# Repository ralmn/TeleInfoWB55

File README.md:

# TeleInfo - ST32WB55

[Version Française / French version](README.FR.md)

This project allows to get the information from the French Linky electric meters (and old meters) via the customer tele-information terminals "TIC" and transmit them in Zigbee. The module is powered by the 150mW dedicated power supply of the Linky.

This repository contains the Kicad sources of the PCB and the sources of the Firmware.

## PCB

The PCB is based on :
* A microcontroller [STM32WB55CCU6](https://www.st.com/en/microcontrollers-microprocessors/stm32wb55cc.html) which takes care of the information retrieval and retransmission in Zigbee
* A diode bridge for the conversion of the AC power supply of the linky into DC.
* A linear regulator LM2937-IMP for the conversion in 3.3V
* One SHA620-A octocoupler for serial link recovery from the TeleInfo
* 2 x 5V power supply pins (5V and GND) for the old counters. With a jumper for the choice between Linky/5V
* 5 pins to flash the microcontroller with a st-link (SWD).

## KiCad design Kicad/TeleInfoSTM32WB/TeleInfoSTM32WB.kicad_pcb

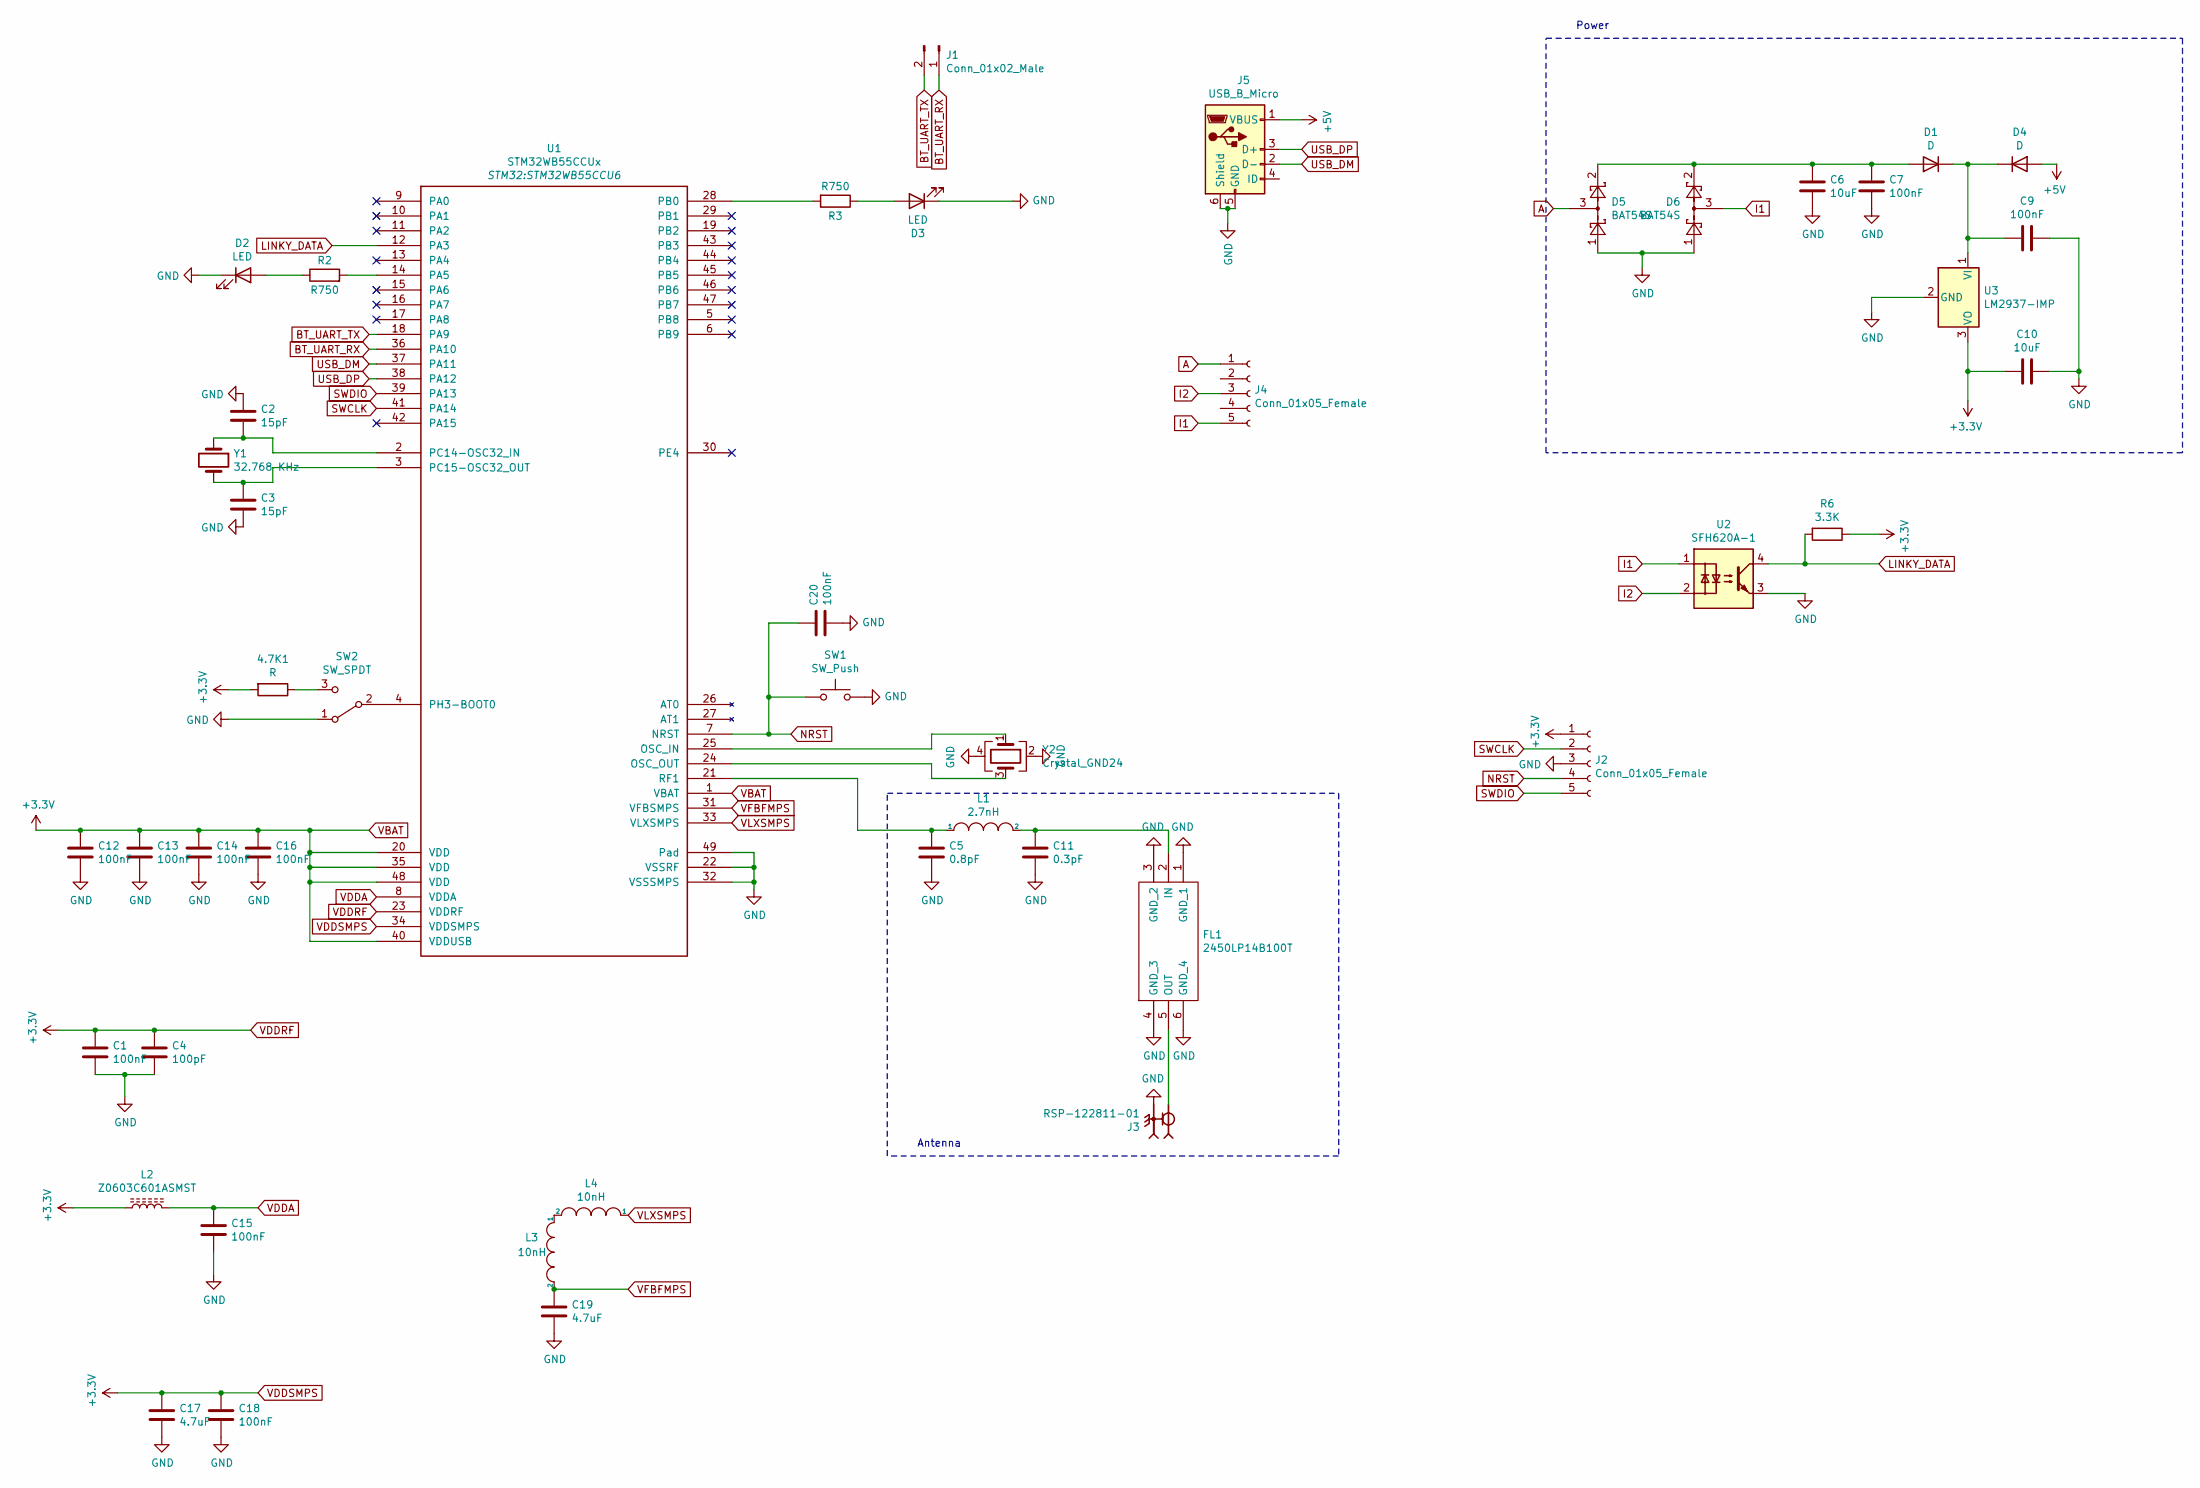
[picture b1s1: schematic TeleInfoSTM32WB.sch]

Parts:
4.7K1: R; R_0805_2012Metric
C1, C7, C9, C12, C13, C14, C15, C16, C20: 100nF; C_0805_2012Metric_Pad1.18x1.45mm_HandSolder; LCSC C138340
C2, C3: 15pF; C_0805_2012Metric_Pad1.18x1.45mm_HandSolder; LCSC C705013
C4: 100pF; C_0805_2012Metric_Pad1.18x1.45mm_HandSolder; LCSC C464454
C5: 0.8pF; C_0805_2012Metric_Pad1.18x1.45mm_HandSolder; LCSC C464454
C6, C10: 10uF; C_0805_2012Metric_Pad1.18x1.45mm_HandSolder; LCSC C89827
C11: 0.3pF; C_0805_2012Metric_Pad1.18x1.45mm_HandSolder; LCSC C138340
C17, C19: 4.7uF; C_0805_2012Metric_Pad1.18x1.45mm_HandSolder; LCSC C464454
C18: 100nF; C_0805_2012Metric_Pad1.18x1.45mm_HandSolder; LCSC C464454
D1, D4: D; D_SOD-123F
D2, D3: LED; LED_0805_2012Metric_Pad1.15x1.40mm_HandSolder; LCSC C389523
D5, D6: BAT54S; SOT-23; LCSC C258194
FL1: 2450LP14B100T; Manufacturer_Part_Number 2450LP14B100T; Mouser Part Number 609-2450LP14B100T
J1: Conn_01x02_Male; PinHeader_1x02_P2.54mm_Vertical
J2: Conn_01x05_Female; PinHeader_1x05_P2.54mm_Vertical; LCSC C358687
J3: RSP-122811-01; SAMTEC_RSP-122811-01; PARTREV H; LCSC C434808
J4: Conn_01x05_Female; PinHeader_1x05_P2.54mm_Vertical; LCSC C180219
J5: USB_B_Micro; USB_Micro-B_Molex_47346-0001
L1: 2.7nH; L_0603_1608Metric_Pad1.05x0.95mm_HandSolder
L2: Z0603C601ASMST; L_0603_1608Metric_Pad1.05x0.95mm_HandSolder
L3, L4: 10nH; L_0805_2012Metric
R2, R3: R750; R_0805_2012Metric_Pad1.20x1.40mm_HandSolder; LCSC C351549
R6: 3.3K; R_0805_2012Metric_Pad1.20x1.40mm_HandSolder; LCSC C352211
SW1: SW_Push; SwitchSPST; LCSC C127404
SW2: SW_SPDT; SW_SPDT_CK-JS102011SAQN
U1: STM32WB55CCUx; STM32WB55CCU6; LCSC C2151725
U2: SFH620A-1; DIP-4_W7.62mm; LCSC C500642
U3: LM2937-IMP; SOT-223-3_TabPin2; LCSC C140265
Y1: 32.768 KHz; Crystal_SMD_TXC_9HT11-2Pin_2.0x1.2mm_HandSoldering; LCSC C409344
Y2: Crystal_GND24; Crystal_SMD_TXC_7M-4Pin_3.2x2.5mm_HandSoldering; LCSC C91742

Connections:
+5V: D4.2 (A), J5.1 (VBUS)
A: D5.3, J4.1
BT_UART_RX: J1.1, U1.36 (PA10)
BT_UART_TX: J1.2, U1.18 (PA9)
GND: C1.2, C2.1, C3.2, C4.2, C5.2, C6.2, C7.2, C9.1, C10.1, C11.2, C12.2, C13.2, C14.2, C15.2, C16.2, C17.2, C18.2, C19.2, C20.2, D2.1 (K), D3.1 (K), D5.1, D6.1, FL1.1 (GND_1), FL1.3 (GND_2), FL1.4 (GND_3), FL1.6 (GND_4), J2.3, J3.G1, J3.G2, J5.5 (GND), J5.6 (Shield), SW1.2, SW2.1 (A), U1.22 (VSSRF), U1.32 (VSSSMPS), U1.49 (Pad), U2.3, U3.2 (GND), Y2.2, Y2.4
I1: D6.3, J4.5, U2.1
I2: J4.3, U2.2
LINKY_DATA: R6.2, U1.12 (PA3), U2.4
NRST: C20.1, J2.4, SW1.1, U1.7 (NRST)
unnamed: 4.7K1.1, SW2.3 (C)
unnamed: C2.2, U1.2 (PC14-OSC32_IN), Y1.1
unnamed: C3.1, U1.3 (PC15-OSC32_OUT), Y1.2
unnamed: C5.1, L1.1, U1.21 (RF1)
unnamed: C6.1, C7.1, D1.2 (A), D5.2, D6.2
unnamed: C9.2, D1.1 (K), D4.1 (K), U3.1 (VI)
unnamed: C11.1, FL1.2 (IN), L1.2
unnamed: D2.2 (A), R2.1
unnamed: D3.2 (A), R3.1
unnamed: FL1.5 (OUT), J3.1
unnamed: L3.1, L4.2
unnamed: R2.2, U1.14 (PA5)
unnamed: R3.2, U1.28 (PB0)
unnamed: SW2.2 (B), U1.4 (PH3-BOOT0)
unnamed: U1.24 (OSC_OUT), Y2.3
unnamed: U1.25 (OSC_IN), Y2.1
SWCLK: J2.2, U1.41 (PA14)
SWDIO: J2.5, U1.39 (PA13)
USB_DM: J5.2 (D-), U1.37 (PA11)
USB_DP: J5.3 (D+), U1.38 (PA12)
VBAT: 4.7K1.2, C1.1, C4.1, C10.2, C12.1, C13.1, C14.1, C16.1, C17.1, C18.1, J2.1, L2.1, R6.1, U1.1 (VBAT), U1.20 (VDD), U1.23 (VDDRF), U1.34 (VDDSMPS), U1.35 (VDD), U1.40 (VDDUSB), U1.48 (VDD), U3.3 (VO)
VDDA: C15.1, L2.2, U1.8 (VDDA)
VFBFMPS: C19.1, L3.2, U1.31 (VFBSMPS)
VLXSMPS: L4.1, U1.33 (VLXSMPS)

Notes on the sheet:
Power
Antenna

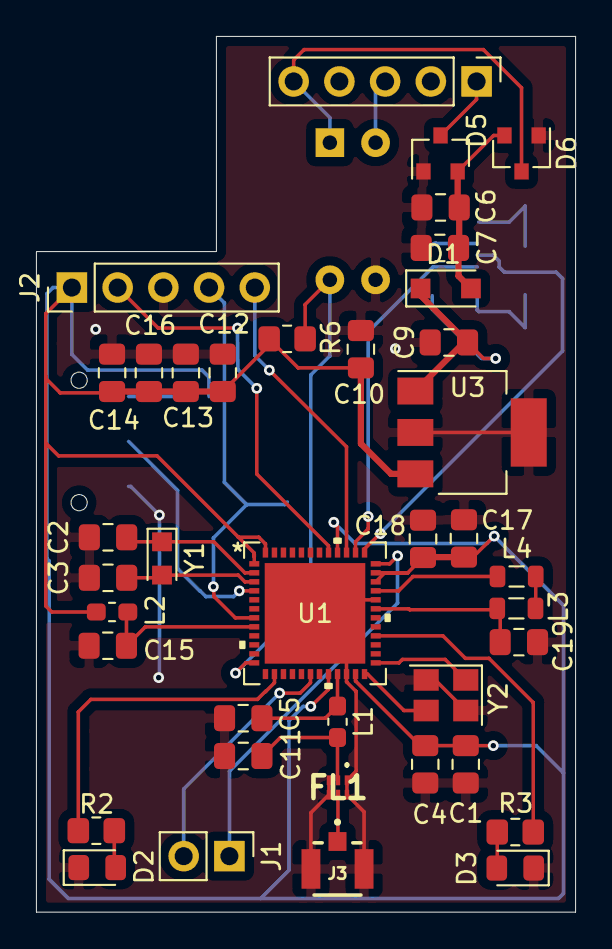
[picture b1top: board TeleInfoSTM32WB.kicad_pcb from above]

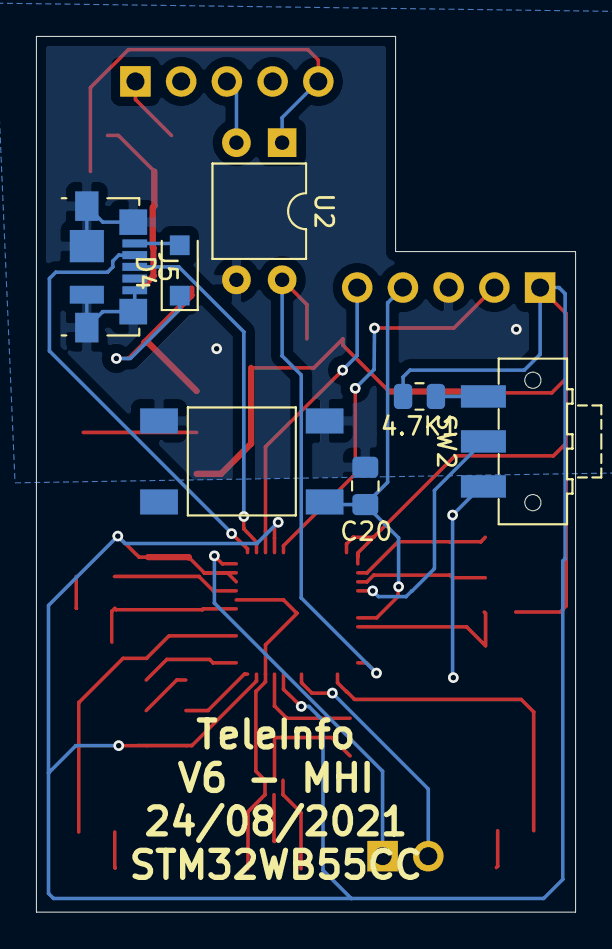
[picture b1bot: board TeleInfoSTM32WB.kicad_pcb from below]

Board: 2 copper layers, 30.0 x 48.6 mm, 46 parts (7 on the bottom side), 33 nets.

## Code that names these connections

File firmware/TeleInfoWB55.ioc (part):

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Mcu.Name=STM32WB55CCUx
Mcu.Package=UFQFPN48
Mcu.UserName=STM32WB55CCUx
PA13.Mode=Serial_Wire
PA13.Signal=SYS_JTMS-SWDIO
PA14.Mode=Serial_Wire
PA14.Signal=SYS_JTCK-SWCLK
PA2.Mode=Asynchronous
PA2.Signal=LPUART1_TX
PA3.Mode=Asynchronous
PA3.Signal=LPUART1_RX
PC14-OSC32_IN.Mode=LSE-External-Oscillator
PC14-OSC32_IN.Signal=RCC_OSC32_IN
PC15-OSC32_OUT.Mode=LSE-External-Oscillator
PC15-OSC32_OUT.Signal=RCC_OSC32_OUT
RCC.HSE_VALUE=32000000
RCC.SYSCLKFreq_VALUE=32000000
board=custom

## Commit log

2021-08-12 Inital commit
2021-08-24 PCB v6
2021-09-01 PCB V6 (forget commited filed.... :clap:)
2021-09-01 Update symbols and footprint libs path + add gitignore + remove useless files
2021-09-01 Update symbol stm32wb55

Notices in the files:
parts and their libraries:
Copyright 2021 Accelerated Designs. All rights reserved.
